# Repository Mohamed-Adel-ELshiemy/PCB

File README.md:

DC motor PCB Design with all files needed and make my foot print from scratch

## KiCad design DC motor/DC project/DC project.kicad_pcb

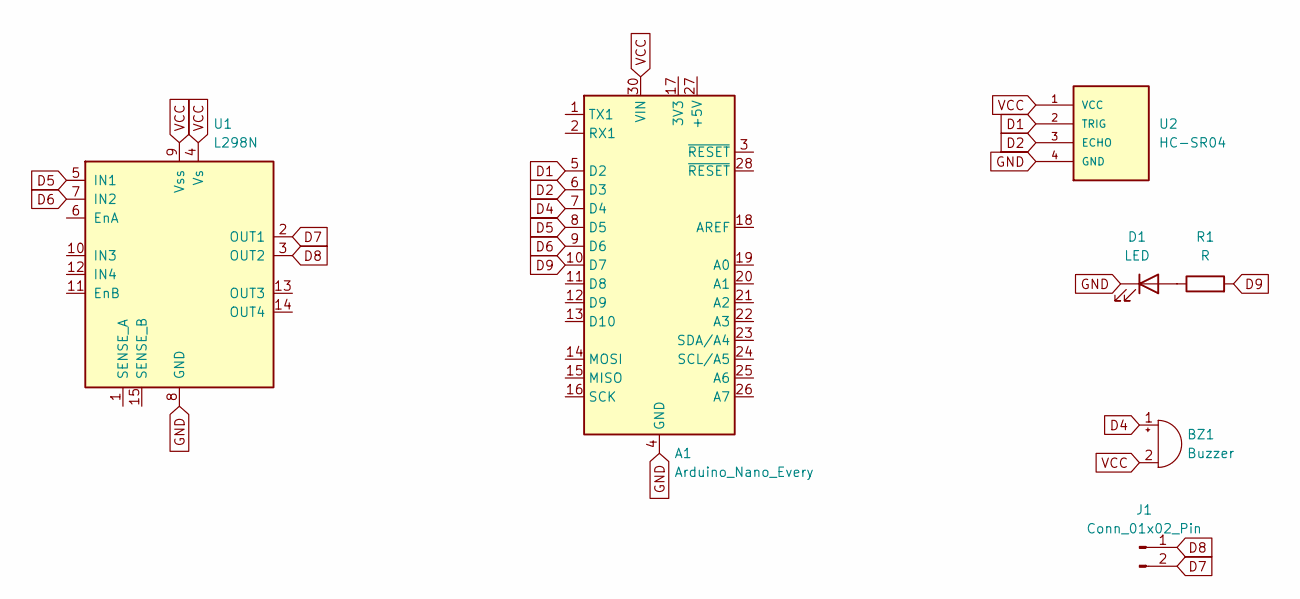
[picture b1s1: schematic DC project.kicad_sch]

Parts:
A1: Arduino_Nano_Every; Arduino_Nano
BZ1: Buzzer; MagneticBuzzer_Kobitone_254-EMB73-RO
D1: LED; LED_D3.0mm
J1: Conn_01x02_Pin; PinHeader_1x02_P2.54mm_Vertical
R1: R; R_Axial_DIN0309_L9.0mm_D3.2mm_P5.08mm_Vertical
U1: L298N; TO-220-15_P2.54x2.54mm_StaggerOdd_Lead4.58mm_Vertical
U2: HC-SR04; XCVR_HC-SR04

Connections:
D1: A1.5 (D2), U2.2 (TRIG)
D2: A1.6 (D3), U2.3 (ECHO)
D4: A1.7 (D4), BZ1.1 (-)
D5: A1.8 (D5), U1.5 (IN1)
D6: A1.9 (D6), U1.7 (IN2)
D7: J1.2, U1.2 (OUT1)
D8: J1.1, U1.3 (OUT2)
D9: A1.10 (D7), R1.2
GND: A1.4 (GND), A1.29 (GND), D1.1 (K), U1.8 (GND), U2.4 (GND)
unnamed: D1.2 (A), R1.1
VCC: A1.30 (VIN), BZ1.2 (+), U1.4 (Vs), U1.9 (Vss), U2.1 (VCC)

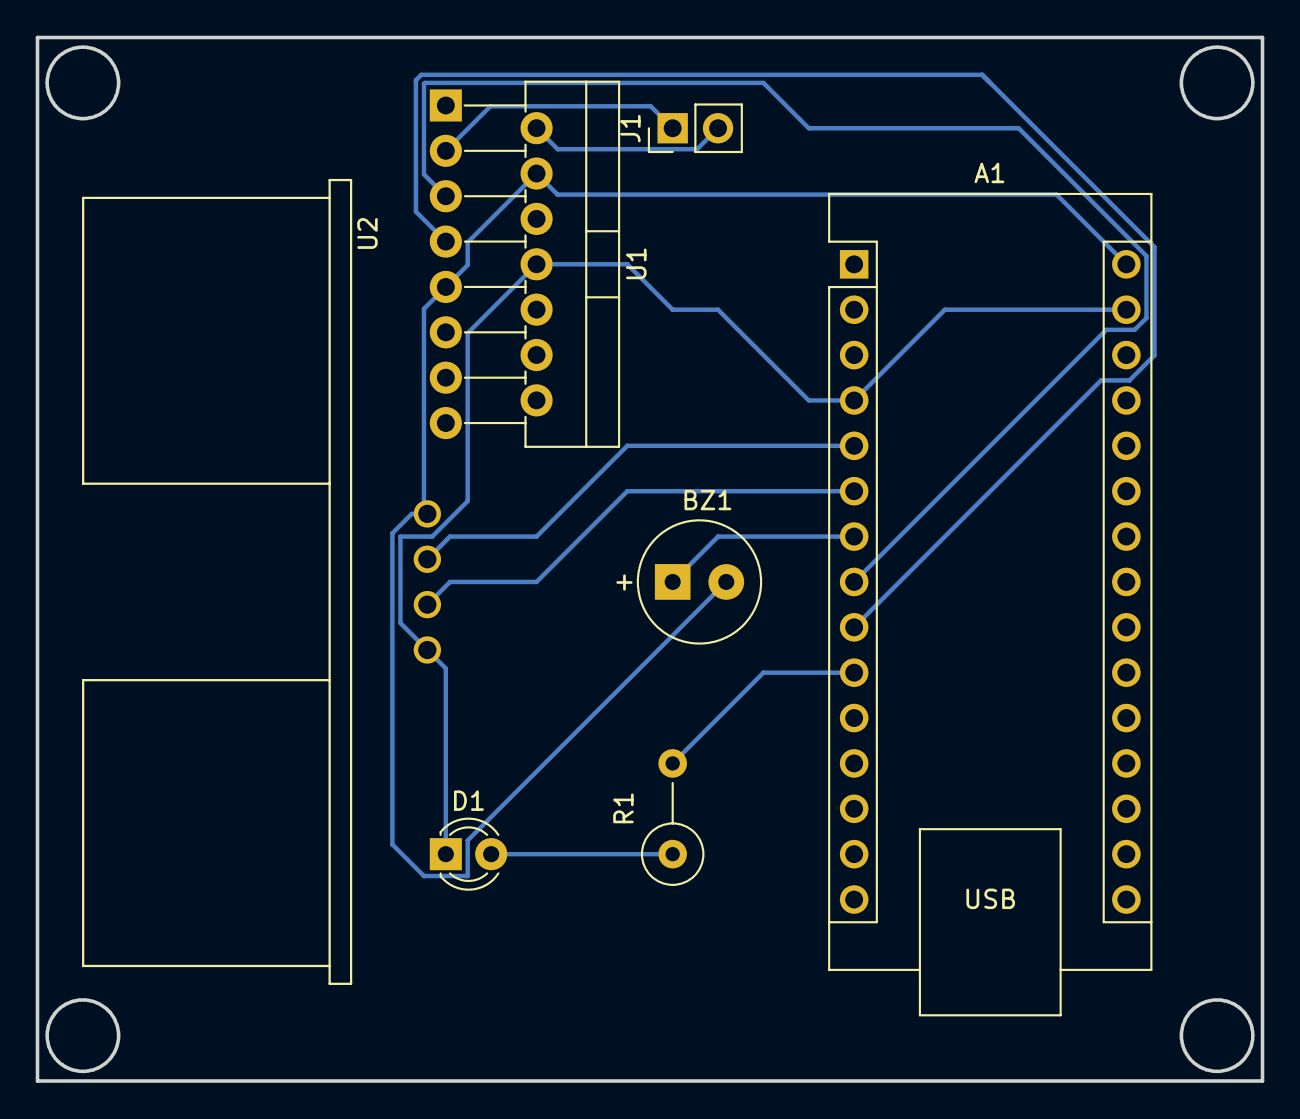
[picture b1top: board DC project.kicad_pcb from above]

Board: 2 copper layers, 68.6 x 58.4 mm, 7 parts (0 on the bottom side), 11 nets.

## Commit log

2024-01-13 PCB commit
